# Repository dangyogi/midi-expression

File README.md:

# midi-expression
Combine custom midi expression board with midi-files for real-time performances.

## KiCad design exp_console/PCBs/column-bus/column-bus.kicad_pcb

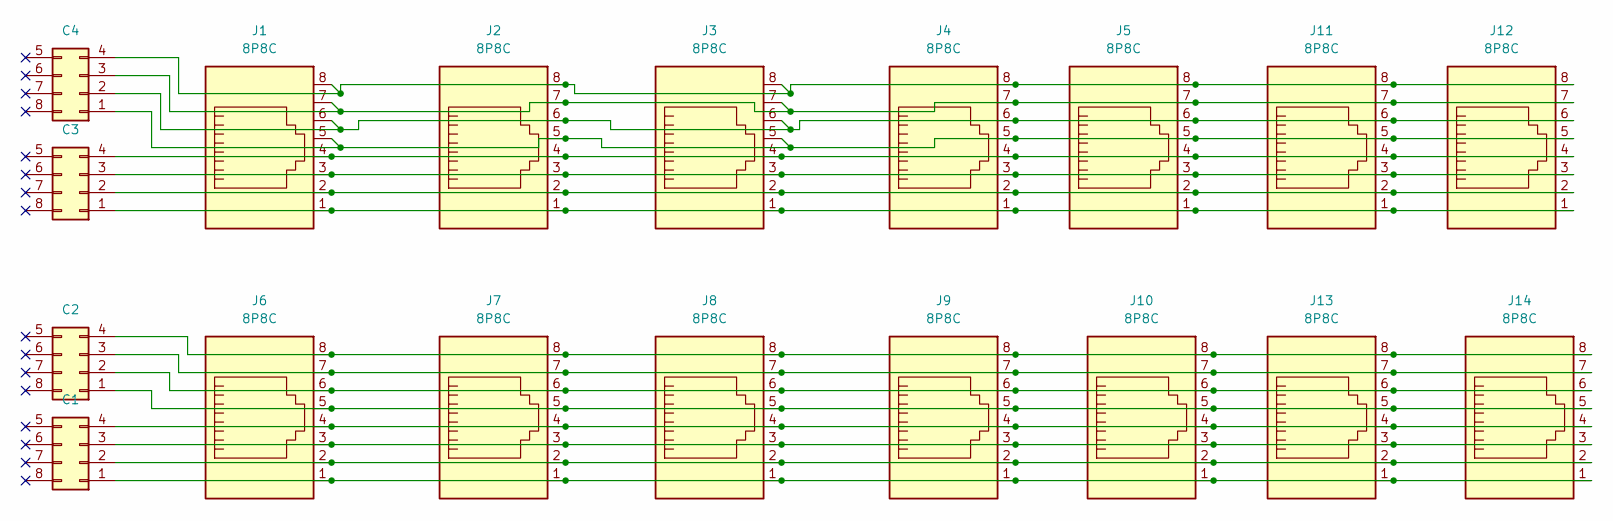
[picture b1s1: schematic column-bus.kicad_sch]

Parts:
C1, C2, C3, C4: Conn_02x04_Counter_Clockwise; Weidmuller-4-vertical
J1, J2, J3, J4, J5, J6, J7, J8, J9, J10, J11, J12, J13, J14: 8P8C; Wurth-8P8C-Vertical

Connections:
unnamed: C1.1, J6.1, J7.1, J8.1, J9.1, J10.1, J13.1, J14.1
unnamed: C1.2, J6.2, J7.2, J8.2, J9.2, J10.2, J13.2, J14.2
unnamed: C1.3, J6.3, J7.3, J8.3, J9.3, J10.3, J13.3, J14.3
unnamed: C1.4, J6.4, J7.4, J8.4, J9.4, J10.4, J13.4, J14.4
unnamed: C2.1, J6.5, J7.5, J8.5, J9.5, J10.5, J13.5, J14.5
unnamed: C2.2, J6.6, J7.6, J8.6, J9.6, J10.6, J13.6, J14.6
unnamed: C2.3, J6.7, J7.7, J8.7, J9.7, J10.7, J13.7, J14.7
unnamed: C2.4, J6.8, J7.8, J8.8, J9.8, J10.8, J13.8, J14.8
unnamed: C3.1, J1.1, J2.1, J3.1, J4.1, J5.1, J11.1, J12.1
unnamed: C3.2, J1.2, J2.2, J3.2, J4.2, J5.2, J11.2, J12.2
unnamed: C3.3, J1.3, J2.3, J3.3, J4.3, J5.3, J11.3, J12.3
unnamed: C3.4, J1.4, J2.4, J3.4, J4.4, J5.4, J11.4, J12.4
unnamed: C4.1, J1.5, J2.5, J3.5, J4.5, J5.5, J11.5, J12.5
unnamed: C4.2, J1.6, J2.6, J3.6, J4.6, J5.6, J11.6, J12.6
unnamed: C4.3, J1.7, J2.7, J3.7, J4.7, J5.7, J11.7, J12.7
unnamed: C4.4, J1.8, J2.8, J3.8, J4.8, J5.8, J11.8, J12.8

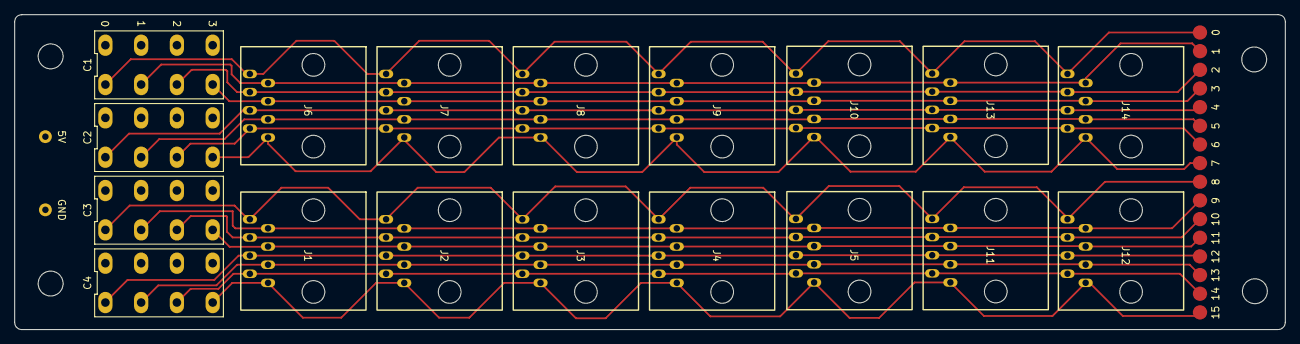
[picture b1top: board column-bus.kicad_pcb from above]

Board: 2 copper layers, 177.7 x 44.0 mm, 18 parts (0 on the bottom side), 16 nets.

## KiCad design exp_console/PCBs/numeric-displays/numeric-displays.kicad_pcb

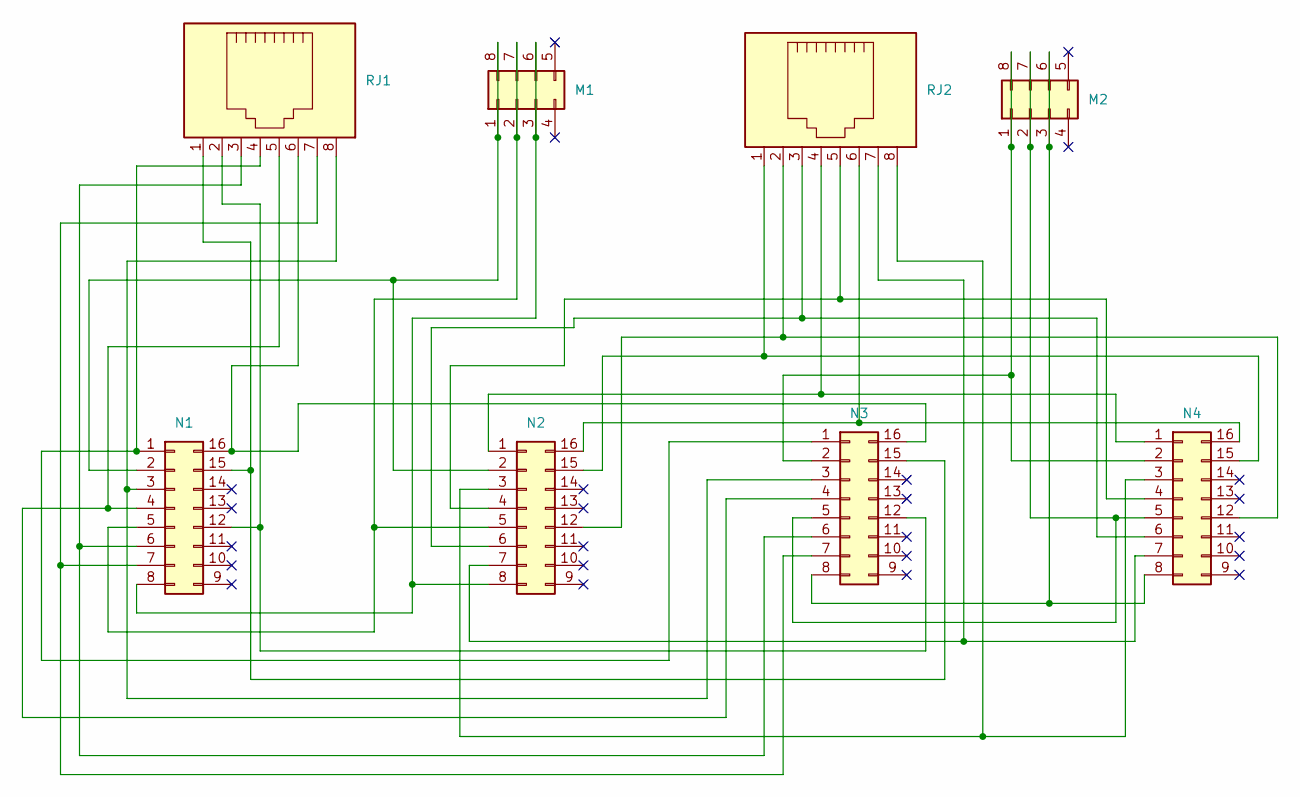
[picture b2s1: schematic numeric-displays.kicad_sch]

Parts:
M1, M2: Conn_02x04_Counter_Clockwise; Weidmuller-4-vertical
N1, N2, N3, N4: Conn_02x08_Counter_Clockwise; DIP-16_W7.62mm_Socket_LongPads
RJ1, RJ2: 8P8C; Wurth-8P8C-Vertical

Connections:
unnamed: M1.1, M1.8, N1.2, N2.2
unnamed: M1.2, M1.7, N1.5, N2.5
unnamed: M1.3, M1.6, N1.8, N2.8
unnamed: M2.1, M2.8, N3.2, N4.2
unnamed: M2.2, M2.7, N3.5, N4.5
unnamed: M2.3, M2.6, N3.8, N4.8
unnamed: N1.1, N3.1, RJ1.4
unnamed: N1.3, N3.3, RJ1.8
unnamed: N1.4, N3.4, RJ1.5
unnamed: N1.6, N3.6, RJ1.3
unnamed: N1.7, N3.7, RJ1.7
unnamed: N1.12, N3.12, RJ1.2
unnamed: N1.15, N3.15, RJ1.1
unnamed: N1.16, N3.16, RJ1.6
unnamed: N2.1, N4.1, RJ2.4
unnamed: N2.3, N4.3, RJ2.8
unnamed: N2.4, N4.4, RJ2.5
unnamed: N2.6, N4.6, RJ2.3
unnamed: N2.7, N4.7, RJ2.7
unnamed: N2.12, N4.12, RJ2.2
unnamed: N2.15, N4.15, RJ2.1
unnamed: N2.16, N4.16, RJ2.6

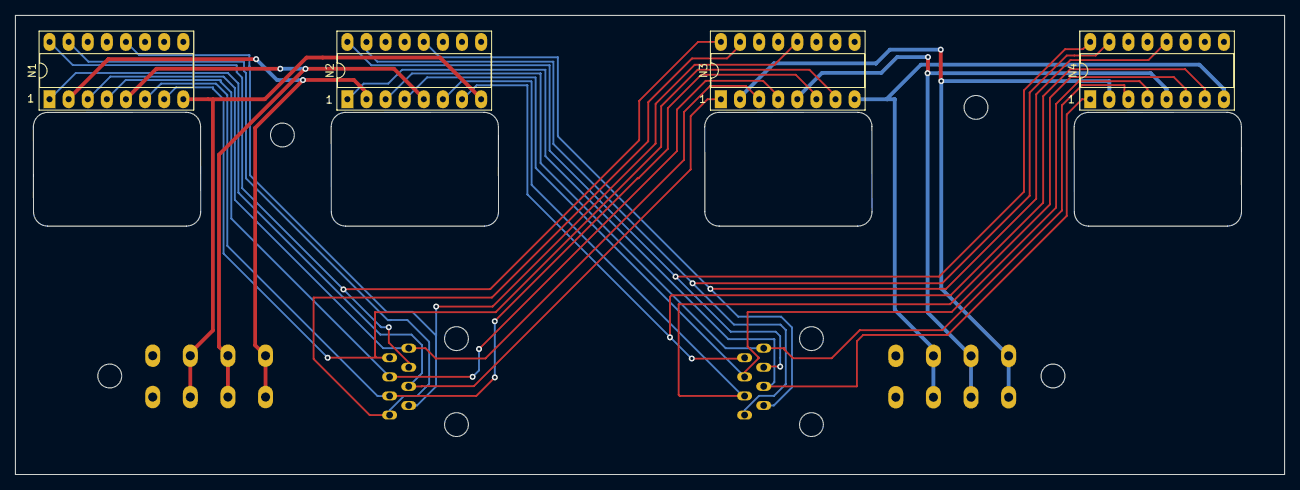
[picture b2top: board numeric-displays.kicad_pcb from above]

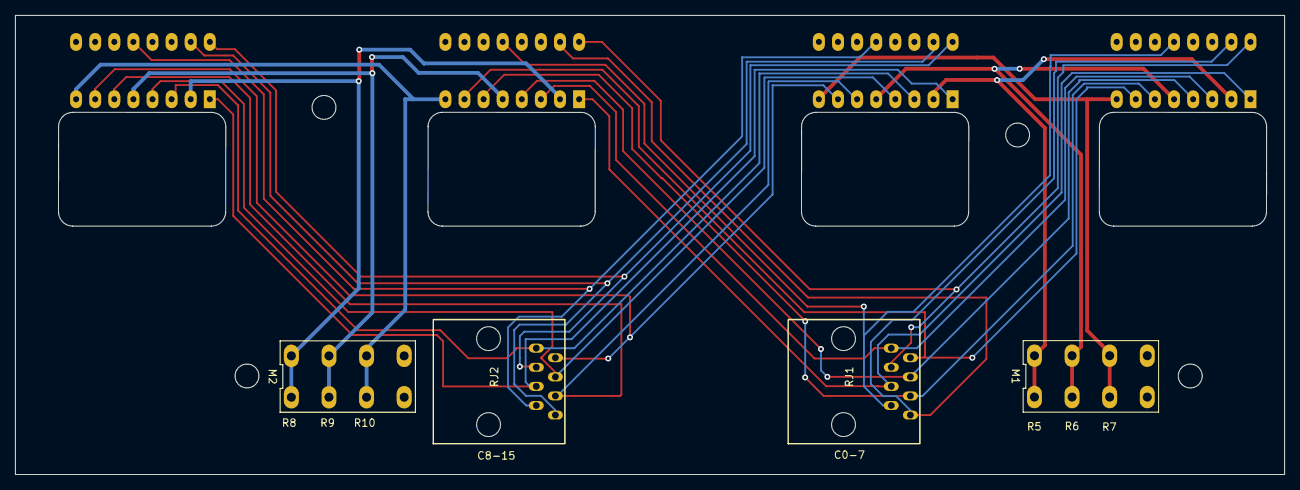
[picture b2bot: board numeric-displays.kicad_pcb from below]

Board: 2 copper layers, 168.7 x 61.0 mm, 8 parts (4 on the bottom side), 22 nets.

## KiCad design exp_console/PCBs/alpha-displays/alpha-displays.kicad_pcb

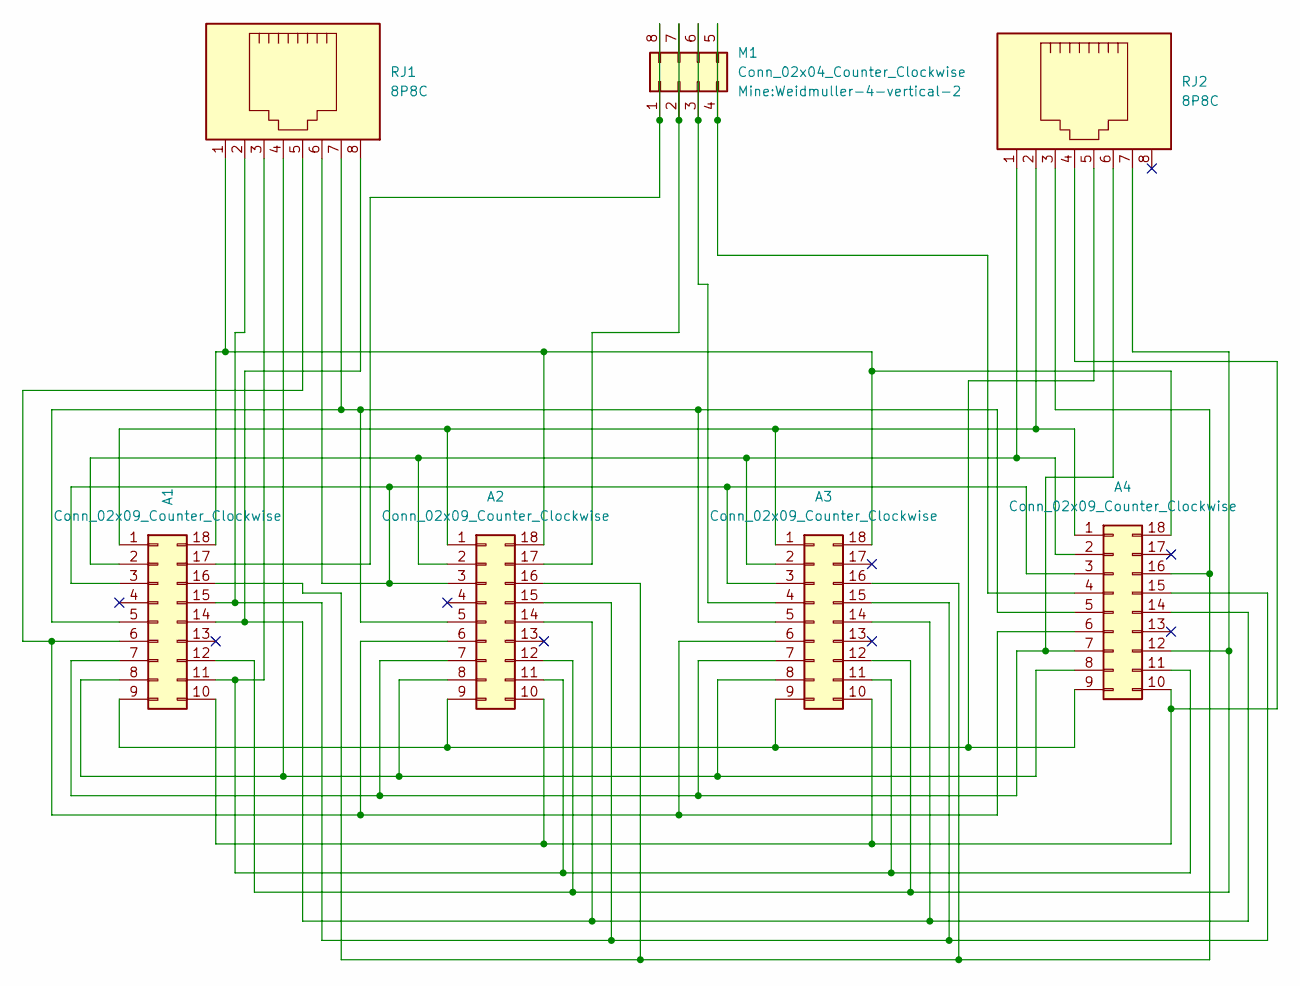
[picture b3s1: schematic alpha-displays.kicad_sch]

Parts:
A1, A2, A3, A4: Conn_02x09_Counter_Clockwise; DIP-18_W7.62mm_Socket_LongPads
M1: Conn_02x04_Counter_Clockwise; Weidmuller-4-vertical-2
RJ1, RJ2: 8P8C; Wurth-8P8C-Vertical

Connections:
unnamed: A1.1, A2.1, A3.1, A4.1, RJ2.2
unnamed: A1.2, A2.2, A3.2, A4.2, RJ2.1
unnamed: A1.3, A2.3, A3.3, A4.3, RJ1.6
unnamed: A1.5, A2.5, A3.5, A4.5, RJ1.7
unnamed: A1.6, A2.6, A3.6, A4.6, RJ1.5
unnamed: A1.7, A2.7, A3.7, A4.7, RJ2.6
unnamed: A1.8, A2.8, A3.8, A4.8, RJ1.4
unnamed: A1.9, A2.9, A3.9, A4.9, RJ2.5
unnamed: A1.10, A2.10, A3.10, A4.10, RJ2.4
unnamed: A1.11, A2.11, A3.11, A4.11, RJ1.3
unnamed: A1.12, A2.12, A3.12, A4.12, RJ2.7
unnamed: A1.14, A2.14, A3.14, A4.14, RJ1.8
unnamed: A1.15, A2.15, A3.15, A4.15, RJ1.2
unnamed: A1.16, A2.16, A3.16, A4.16, RJ2.3
unnamed: A1.17, M1.1, M1.8
unnamed: A1.18, A2.18, A3.18, A4.18, RJ1.1
unnamed: A2.17, M1.2, M1.7
unnamed: A3.4, M1.3, M1.6
unnamed: A4.4, M1.4, M1.5

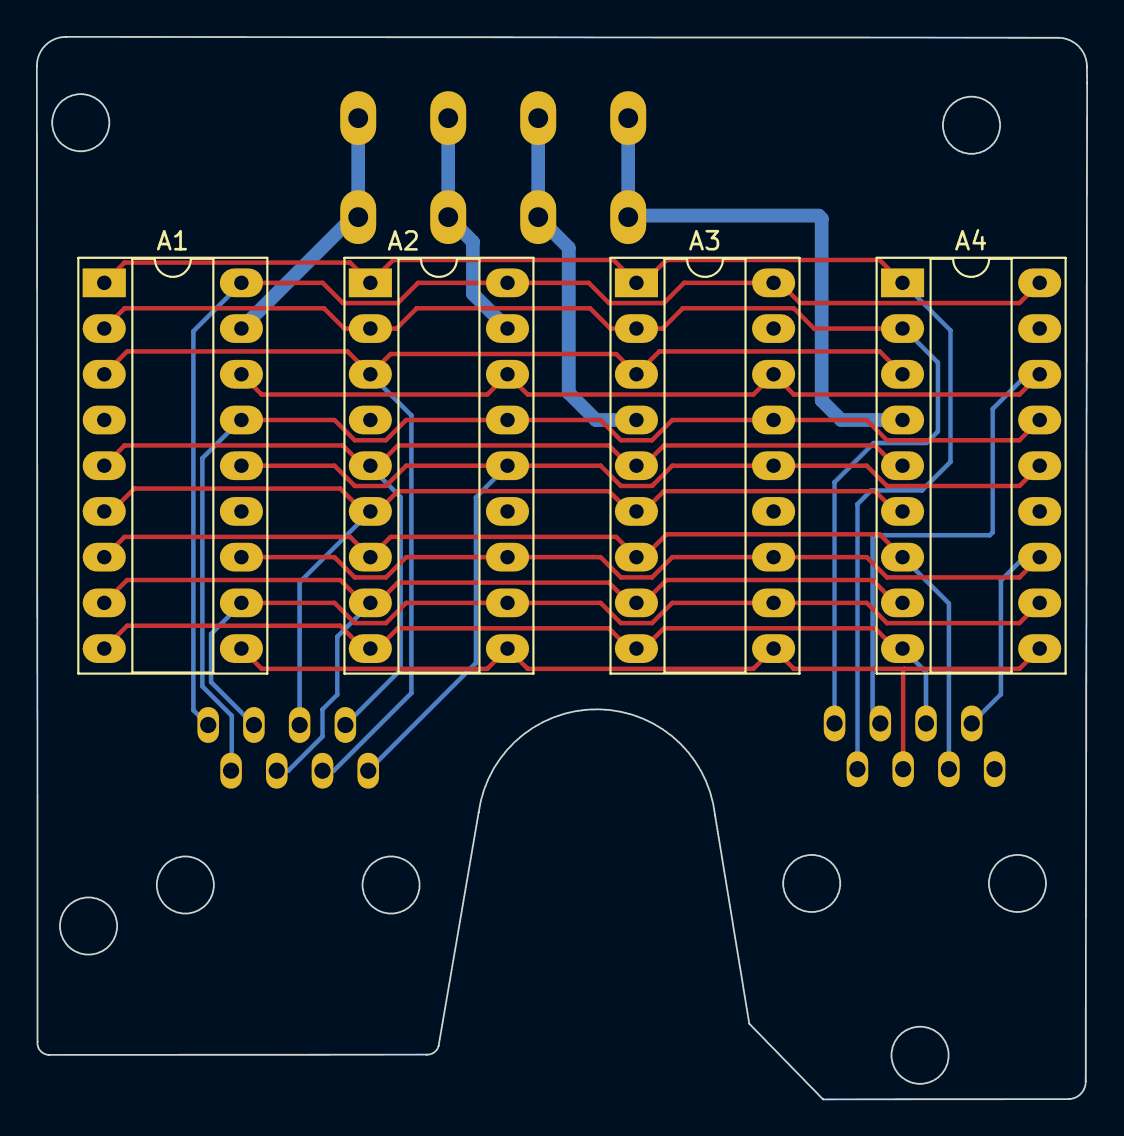
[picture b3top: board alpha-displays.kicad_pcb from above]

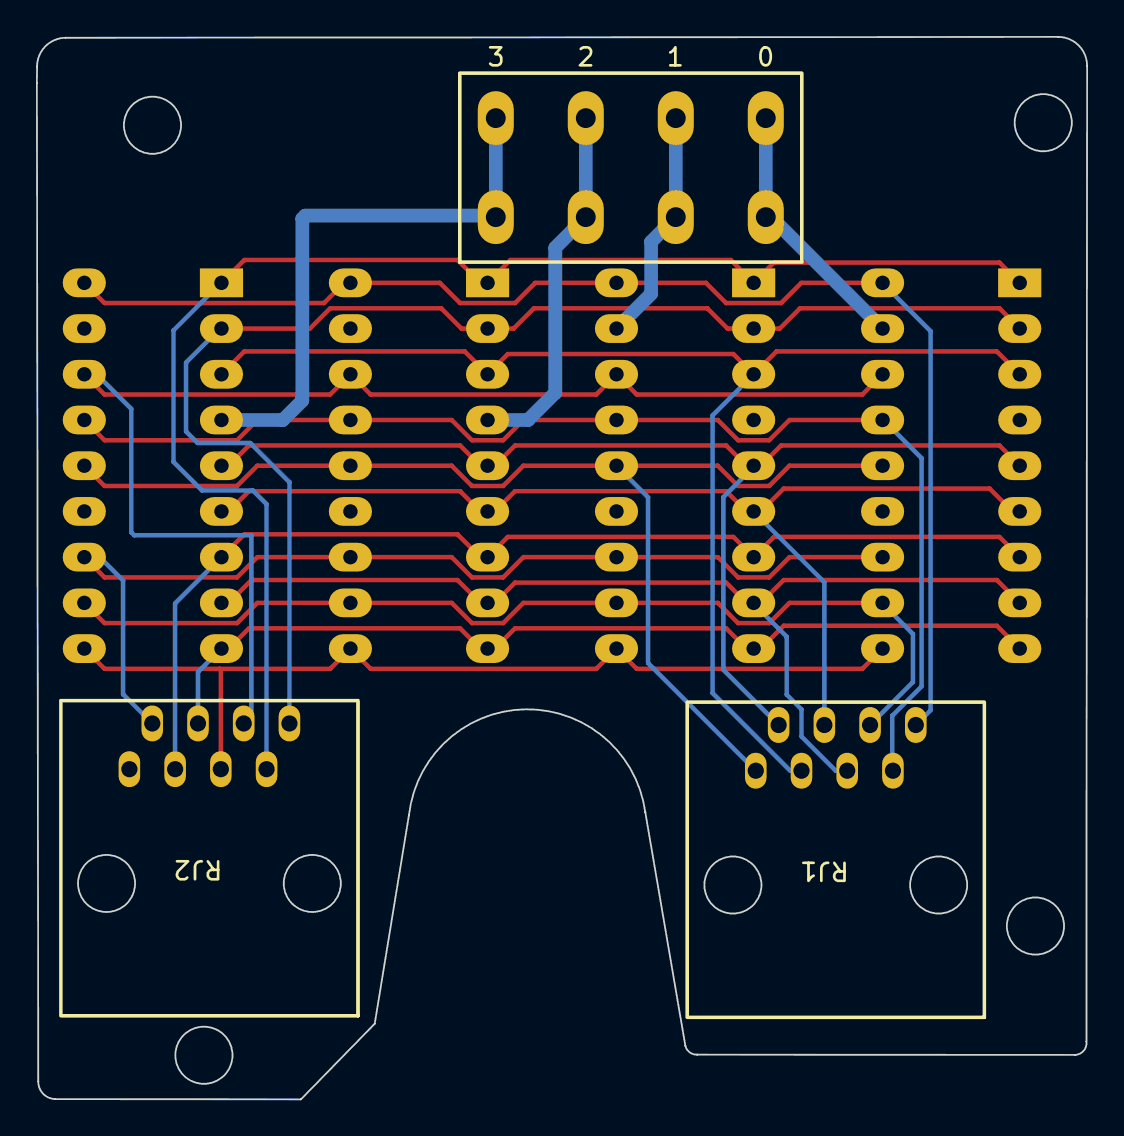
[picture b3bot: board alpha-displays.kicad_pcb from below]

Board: 2 copper layers, 58.3 x 59.0 mm, 7 parts (3 on the bottom side), 19 nets.

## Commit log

2022-04-20 Initial commit.
2022-04-21 Switched to queues for MIDI events. No longer drops MIDI events!
2022-05-08 Checkpoint.
    Got MIDI_CONTROL_ASSIGNMENTS done and Actor recalc logic done. Ready to add MIDI control
    setting changes. Started on scaling volumes in synth.py, but they aren't the same (yet) in
    the midi file, so waiting on that until I get the MIDI editor installed and figured out...
2022-05-08 Several little cleanups. Chief one is getting ^C working right!
2022-05-08 Added empty funs for each control change, wired to distribution code.
2022-05-14 Got notes.py and tuning_systems.py tested!
2022-05-14 Added cents_per_octave to tuning_systems to get fudged octaves.
    Not fully tested yet, but passing all current tests.
2022-05-15 Finished testing tuning_systems.py.
2022-05-15 Cleaned up tuning_systems.py as program, examined output. Set Meantone.
2022-05-19 Got all synth settings defined in synth_settings.yaml prior to implementing them.
2022-05-22 Checkpoint after writing gen_synth_settings.py
2022-05-22 Added more verification in gen_synth_settings.py
2022-05-22 empty shell gen_synth_settings.py
2022-05-23 gen_synth_settings.py starting to work (doesn't bomb)
2022-05-23 First attempt at Linked_chain iterator.
2022-05-23 Better version of Linked_chain!
2022-05-23 Finished redoing channel.py and renamed to notify.py
2022-05-25 Finished coding envelope.py (but not tested!).
2022-05-25 This got left behind...
2022-05-25 Got pytests to pass.
2022-05-25 Checkpoint Envelope tests. All passing, but still need Sin tests.
2022-05-25 All Envelope tests done and passing!
2022-05-26 Wrote test_utils.py and got it working.
2022-05-26 Fixed cross-test contamination.
2022-05-26 Integrated new Envelope with synth.py (not tested yet)
2022-05-26 Finished integration of Envelope into synth, old pytests passing.
    But still no synth pytests.
2022-05-26 Got synth working again with Bach Prelude...
    But fudged ampl_offset in Harmonic class. Probably needs to be
    done differently so that changes in ampl_offset take immediate effect.
2022-05-26 Integrated generated synth_settings.py into synth.py,
    still plays Bach prelude and passes all pytests.
2022-05-29 Fixed setting bug, now clipping output to soundcard.
2022-06-04 checkpoint. Work started on further .yaml file formats.
2022-06-05 Checkpoint sketch_pots. Only one FIX left...
    Still haven't tested actual pot(s)...
2022-06-07 Checkpoint parse_wiring.py
2022-06-07 Almost finished with parse_wiring.py
    Need to work some on the formatting for showing the connections to a part.
2022-06-12 Paper signage done.
2022-06-15 Front panel done. exp_console.yaml updated. Sketch_pots coded...
    Still need to complete "list" type in parse_wiring.py.
2022-06-17 Got the wiring related stuff hopefully finalized.
2022-06-19 Good start on sketch_leds.
2022-06-20 Checkpoint, trying to break up sketch_leds into smaller pieces...
2022-06-20 Got sketch_leds to compile! ...
    Still need to check the need for header files.
2022-06-20 Checkpoint before renaming several files in sketch_led/
2022-06-20 Renamed files in sketch_led/ to shorten their names.
2022-06-21 Looks like sketch_pots is working! (and tested, except for I2C)
2022-06-23 Good start on sketch_master.
2022-06-24 Testing first switch col for sketch_master.
2022-06-24 Added display commands to sketch_led, got it to compile.
2022-06-25 Finished INTERFACE and Errno assignments in sketch_leds...
    Also some debugging enhancements in sketch_master.
2022-06-28 Misc cleanup, and added test commands to sketch_leds.
2022-06-29 Got notes working.
2022-06-29 Added internal numbers to console parts ...
    in prep for code gen on master controller.
2022-07-01 Checkpoint master controller code generation.
2022-07-05 checkpoint, sketch_leds loaded, initial debugging...
    Work on update.{h,ino} templates. update.h should be close now.
2022-07-06 More work on update.{h,ino} templates. Getting close!
2022-07-07 Got update.{h,ino} moved further along (wrote display logic)...
    Still need to write update function in update.ino...
2022-07-16 Checkpoint conversion to teensy. Just needs to be compiled and tested...
2022-07-20 Added RAM controller & updated Master controller program.
2022-07-21 Added I2C tests from Serial to sketch_master to/from RAM controller.
2022-09-17 Added PCB layout files.
2023-08-22 Snapshot debugging I2C --
    going to do significant changes to sketch_led.ino for sendReport
    so that it no longer queues it. The Wire library requires the sendReport
    processing (i.e., Wire.writes) to be complete before the function
    returns.
2023-08-24 Got I2C working to LED controller, started driver.
2023-08-26 byte transfer tests work. driver initialization works.
2023-08-26 Added first iteration of user_requests.py -- just h command for now
2023-10-29 Added changes for new column mapping to Arduino pins.
    For PCB layout.
2023-10-30 Added easyEDA PCB file for LED Controller.
2023-11-29 New LED Controller board passing initial tests.
2023-11-30 Finished testing for LED Controller PCB.
2023-12-29 Checkpoint alpha & numeric display debug, V17
2023-12-29 Checkpoint alpha/numeric debug V18
2023-12-29 Added letters.py (generated file) to repo
2023-12-30 Checkpoint alpha/numeric debug V20
2023-12-30 alpha/numeric debug finished V21
2023-12-30 Added testing mode commands to turn on 1 col/row. V23
2024-01-01 Checkpoint alpha/number debug, V24
2024-05-09 Checkpoint after replacing rotary encoders.
    Many changes not compiled yet...
2024-05-11 Did debounce tests/measurements, loaded new sketch_master (V8).
2024-05-15 Last commit before new master controller board.
    Fixed encoder decode bug. Added Trace_encoders.
2024-05-21 Checkpoint getting displays working.
2024-05-22 Displays starting to work. Harmonic funs not specified.
2024-05-25 Added function encoder value memory and defaults...
    Seems to be working. Now at Master V37.
2024-06-09 Checkpoint. Working on reading pot values in master.
2024-06-10 Looks like Master <- Pots I2C is working now!
2024-06-12 Checkpoint: added midi_control.ino, but not wired in yet.
2024-06-15 Coding complete on exp_console, but still needs debugging!
2024-07-29 Checkpoint on test_arduino.
    Compiles sketch_master on laptop. Need to add socket comms and stub functions...
2024-08-01 Checkpoint. Getting close to generating tmp/test!
    run_test.py generates tmp/test.cpp which compiles with no warnings.
    Only thing left on C++ side is implementing run_to_return in utils.cpp???
    Then writing the scripting engine (in python)...
2024-08-02 Finished coding C++ part. No testing yet.
2024-08-02 Moved sketch related files to sketch dir.
2024-08-02 Added init_sketch.cpp to initialize EEPROM.
2024-08-02 run_test.py now removes and recreates tmp dir at startup.
2024-08-02 preliminary end-to-end testing.
2024-08-02 Added send_functions from C++ to test_driver.
2024-08-04 Checkpoint. Finished manual pass through setup()!
    Got get_global coded, not tested. Still need set_global.
2024-08-04 Got "get" command working with Debounce_period.
2024-08-06 Added and tested readline completer in test_driver.
2024-08-06 Added "set" interactive command to test_driver.
    Simple test worked.
2024-08-08 Checkpoint debugging first test scripts...
2024-08-09 Added Lookups and Reports. Reports work from command line.
    Not tested from script yet.
2024-08-10 pass-through starting to work...
2024-08-16 Rewrote test_driver request/response handling.
    Still lots of old code that needs to be deleted (in next commit).
2024-08-16 Deleted dead code from test_driver.py
2024-08-16 Added lookups to Function parameters.
    To translate back parameter values back to #define names for readability.
2024-08-16 Added fun_name to 'returned' cpp_command.
2024-08-16 Added fun_names to 'return' commands.
2024-08-17 Fixed bug in sketch_master. Report encoders now incl min/max.
2024-08-17 Fixed display of final 'returned' when not in verbose mode
2024-08-17 Added sendRequest history and fixed SIGSEGV in functions.ino
2024-08-24 Added hooks for usb-midi testing.
2024-08-24 Test pots done.
2024-08-25 Note testing written and passing.
2024-08-26 Channel functions tested.
2024-08-26 Harmonic functions tested and passing. Testing done!
2024-08-26 Added Trace flag to turn_on_periodic_fun to shut down prints.
    This is sketch_master V61, loaded onto teensy.
    Also wrote snapshot sh script to capture all test output.
